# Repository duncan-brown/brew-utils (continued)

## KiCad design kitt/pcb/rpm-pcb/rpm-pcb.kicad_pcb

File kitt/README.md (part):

# kitt

The software that drives the KITT dashboard. Two pieces:

- [`panp/panp.py`](panp/panp.py) — the daemon that runs on both Raspberry Pis
  and puts brewery data onto the dash gauges.
- [`switchpod/`](switchpod/) — Arduino firmware that reads the dash keypads.
  How a pod reaches the Pi is in [switchpod/README.md](switchpod/README.md).

PANP stands for Power / Auto / Norm / Pursuit, the four buttons on the dash.

This file is about how the software works. For what each gauge on the dash
means — KITT's labels against the brewery values behind them — see
[DASHBOARD.md](DASHBOARD.md).

## One script, two Pis

`panp.py` is installed identically on both machines and decides what it is at
startup from `socket.gethostname()`. Anything else exits with an error.

| | `rpints` | `brewpi` |
| --- | --- | --- |
| Loop class | `RPintsLoopHandler` | `BrewPiLoopHandler` |
| Reads | 6 keezer + 3 lager probes, RaspberryPints MySQL | mash + HLT probes, 3 BrewPi Remix instances |
| Drives | tacho, red dummy3, dummy6 | speedo, message center, red/green dummy3 |
| Owns | PANP buttons and lamps, dash power relays, the Hue bench and room lights | flow meter relays |
| Mode GPIO | output (tells `brewpi` the mode) | input (follows `rpints`) |

Shared between them: `read_probe_f` and the `get_temps` thread,
`BrightnessHandler`, `Bus` and `Wire` (the serial ports and the gate that
paces writes to them), `Service` (systemd
notification and shutdown), and the pin constants at the top of the file.
`main()` calls `setup_rpints` or `setup_brewpi` and then runs the loop.

## Structure

Everything slow runs in a daemon thread and communicates with the main loop
through a `Queue`. The main loop never blocks on I/O.

```
  ┌────────────────────┐
  │ get_switchpod()    │  reads /dev/switchpod, one digit per keypress
  ├────────────────────┤
  │ get_temps()        │  polls one-wire probes once a second
  ├────────────────────┤        ┌───────────┐      ┌──────────────┐
  │ get_brewpi_rmx_... │───────▶│  Queues   │─────▶│ loop_handler │────▶ serial
  └────────────────────┘        └───────────┘      │  .loop()     │      to dash
                                                   └──────────────┘
                                                    every 0.25 s
```

Each `loop()` call drains its queues with `drain(q)`, recomputes what should
be on screen, and writes it out. Queue entries are `(index, value)` tuples.

The Hue lights run the other way round: `PANPHandler` queues an on or off
request for the bench light from the button callback, the loop handler
queues one for the room lights when a right-pod key asks, and the
`HueLight.loop()` thread talks to the Hue bridge, which is in another part of
the building. A slow or absent bridge can therefore never hold up the dash.

The database is polled less often than everything else: `RPintsLoopHandler`
counts passes and only queries RaspberryPints once every `DATABASE_EVERY`
passes, which is eleven.

## The PANP modes

Pressing a PANP button on `rpints` moves power relays and flips the two GPIO
lines that `brewpi` watches, so both Pis change behaviour together.

| Mode | Dash | Message center |
| --- | --- | --- |
| **Auto** | off (relays cut power to upper and lower dash) | stays on, showing `BREWPI UP` and flow meter status |
| **Norm** | on, dimmed | captions the lower display |
| **Pursuit** | on, full brightness, switch pod lamps lit, bench light on | captions the lower display |

Leaving Auto clears every display and re-sends brightness, because the boards
were unpowered and have lost their state.

Pursuit also switches on the Hue light strip over the brewery workbench, at
full brightness and a chosen white, so there is enough light to read small
print; Norm and Auto switch it off, as does halting the Pis. Two keys on the
right switch pod, `P IND` and `EJECT R`, switch the brewery's room lights on
and off the same way. `rpints` talks to the Hue bridge's v2 API directly, from
a worker thread. It is optional and is configured by
`/usr/local/etc/panp-hue.json`, which is not in this repository because it
holds the bridge's application key; without the file nothing happens, which
is the case on `brewpi`. Setting it up, including getting a key from the
bridge, choosing the colour temperature and listing the room lights, is in
[panp/README.md](panp/README.md).

The Power button is not software at all. It triggers a latching relay that
switches the whole 12 V supply, and each Pi holds an interlock relay *open*
while it is up, taking the button out of the circuit — so nothing can be
switched off without halting both Pis first. That is `power-relay-*.service`
(opens the interlock at boot) and `power-off-*.sh` (releases it during
shutdown). The wiring is in [../HARDWARE.md](../HARDWARE.md#the-power-button).

## Switch pod buttons

Each switch pod is a resistive keypad read by an Arduino, which prints a
position 0–9 over serial; `panp.py` reads them from `/dev/switchpod` in
`get_switchpod()` and queues them for the loop handler.

Even positions are the pod's left column, odd positions the right — which is
why each handler treats `sp_val` 0/2/4/6/8 as one family and 1/3/5/7/9 as
another. The **right** pod (`rpints`) drives the tacho digits and arc: its
left column is one key per keg, showing the imperial pints left and then the
US gallons left before returning to the keezer mean, its right
column shows the three lager probes, and its last two keys switch the brewery
room lights over the Hue bridge — except that in Pursuit `P IND` cycles the
bench light's colour instead. Coming up from Auto resets the tacho to the
mean. The **left** pod (`brewpi`) selects what the lower speedo display shows
and toggles the flow meter relays. Toggling a flow meter flashes `FLOW n on` on
the message center for a second, then restores the normal caption.

Full button-by-button tables, with photographs of both pods, are in
[DASHBOARD.md](DASHBOARD.md).

## Talking to the dash

The boards are serial slaves at 57600 baud on `/dev/ttyAMA0` and `/dev/ttyAMA1`,
addressed by a letter — `A` tacho, `B` speedo, `C` message center, `E`/`F`
dummy3, `G` dummy6. A command looks like:

```
>ABp3C?
 │││ └── payload: hex byte pairs
 ││└──── register: which value on that board
 │└───── command: B write byte, H write hex sequence, S write string
 └────── destination board
```

so `>ABp3C?` means "tacho, write byte, register p (the seven-segment value),
0x3C". Values are scaled to bytes before sending — `tacho_bar`, `lager_bar`,
`keg_bar` and `temperature_bar` map a temperature or a percentage onto the
bargraph steps by walking a list of thresholds, which is where the dash gets
tuned.

The protocol is Paolo Sancono's and the full specification comes with the
boards — but note that the tacho and speedo registers this code writes are
**not in that specification**. The shipped firmware could not set those displays
from a host at all, so in 2023 the commands were added to it: user-value
registers for the tacho's bars and seven-segment, and for the speedo's two
bargraphs and both digit groups. Paolo holds that modified firmware and is free
to ship it. When one of these commands needs checking, the board firmware is the
authority, not the protocol PDF.

That firmware is confidential to Paolo and is not in this repo. Keep it that
way: describing what a command *does* is fine, quoting or paraphrasing his
source is not.

Two things worth knowing before editing the serial code:

- **Every write is preceded by a 0.1 s gap, and a Pi sends one packet at a
  time across both of its buses.** Without the gap the boards drop messages;
  and the two buses share a level shifter that corrupts a packet on one when
  the other is transmitting. Both rules live in `Bus.write`, which takes a
  first-come-first-served turn on the shared `Wire`, so every write gets the
  gap and a burst from one thread cannot starve the other.
- **Hex payloads must be exactly the right length** — four byte pairs for the
  speedo's upper digits, five for the lower, one per bar for the bargraphs.
  A payload of the wrong length is ignored silently rather than rejected.

## The BrewPi side

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
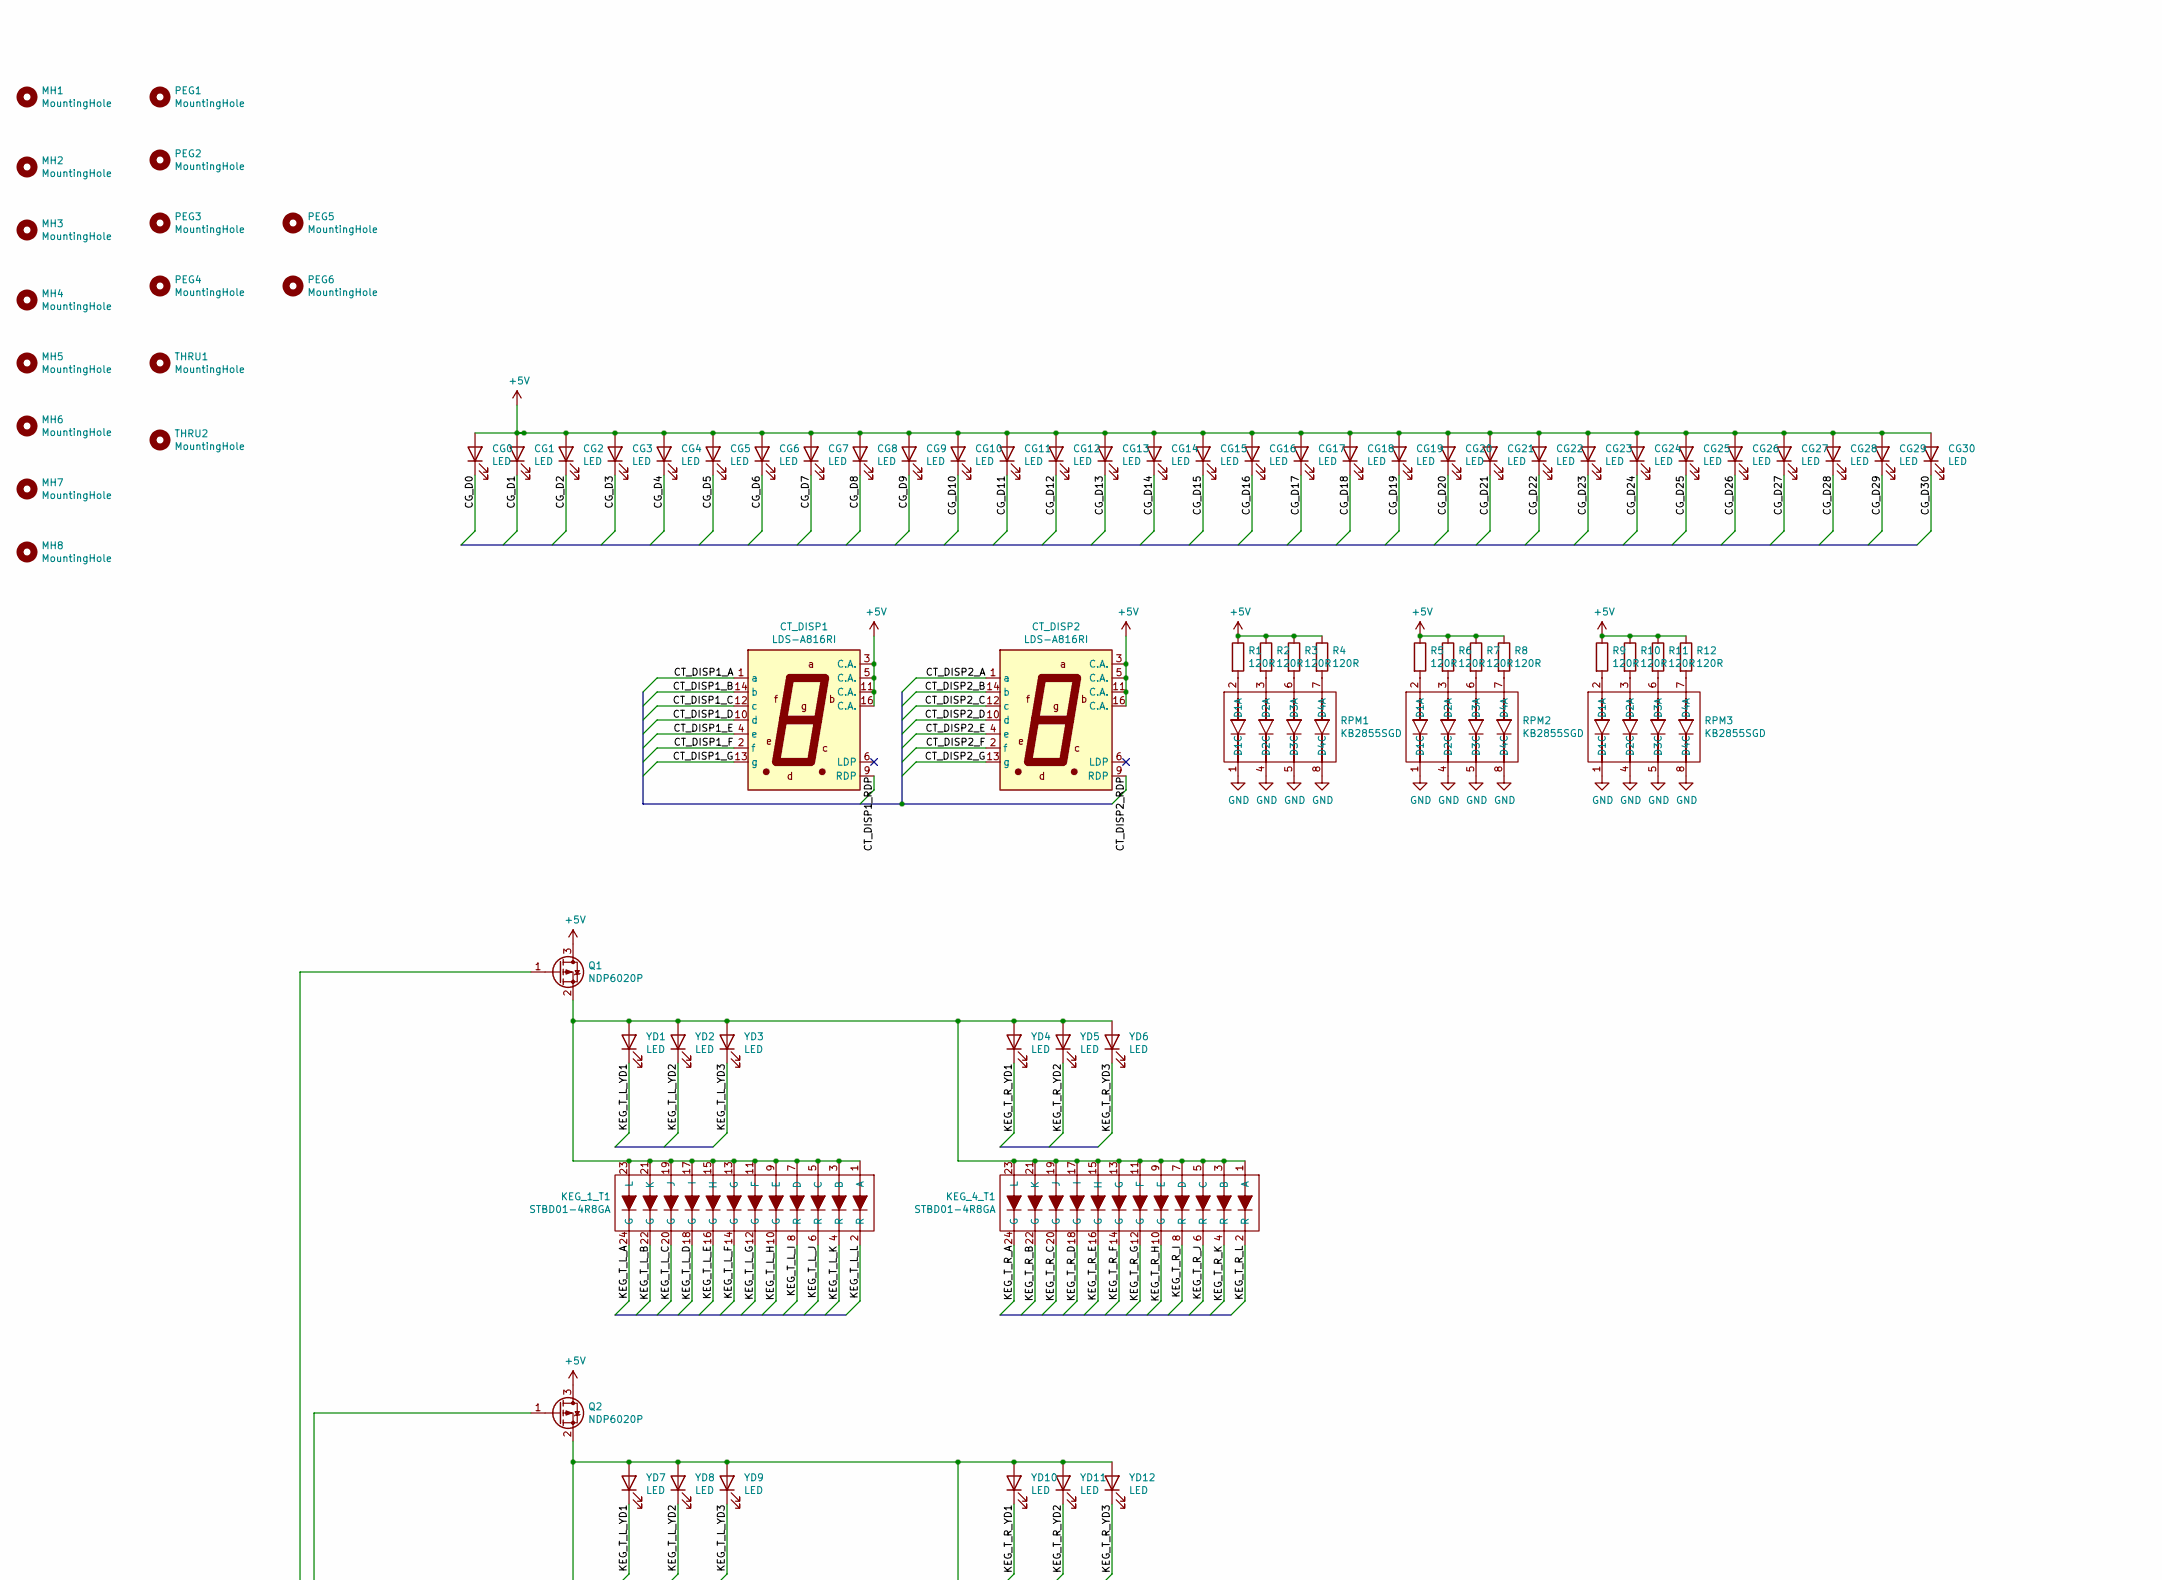
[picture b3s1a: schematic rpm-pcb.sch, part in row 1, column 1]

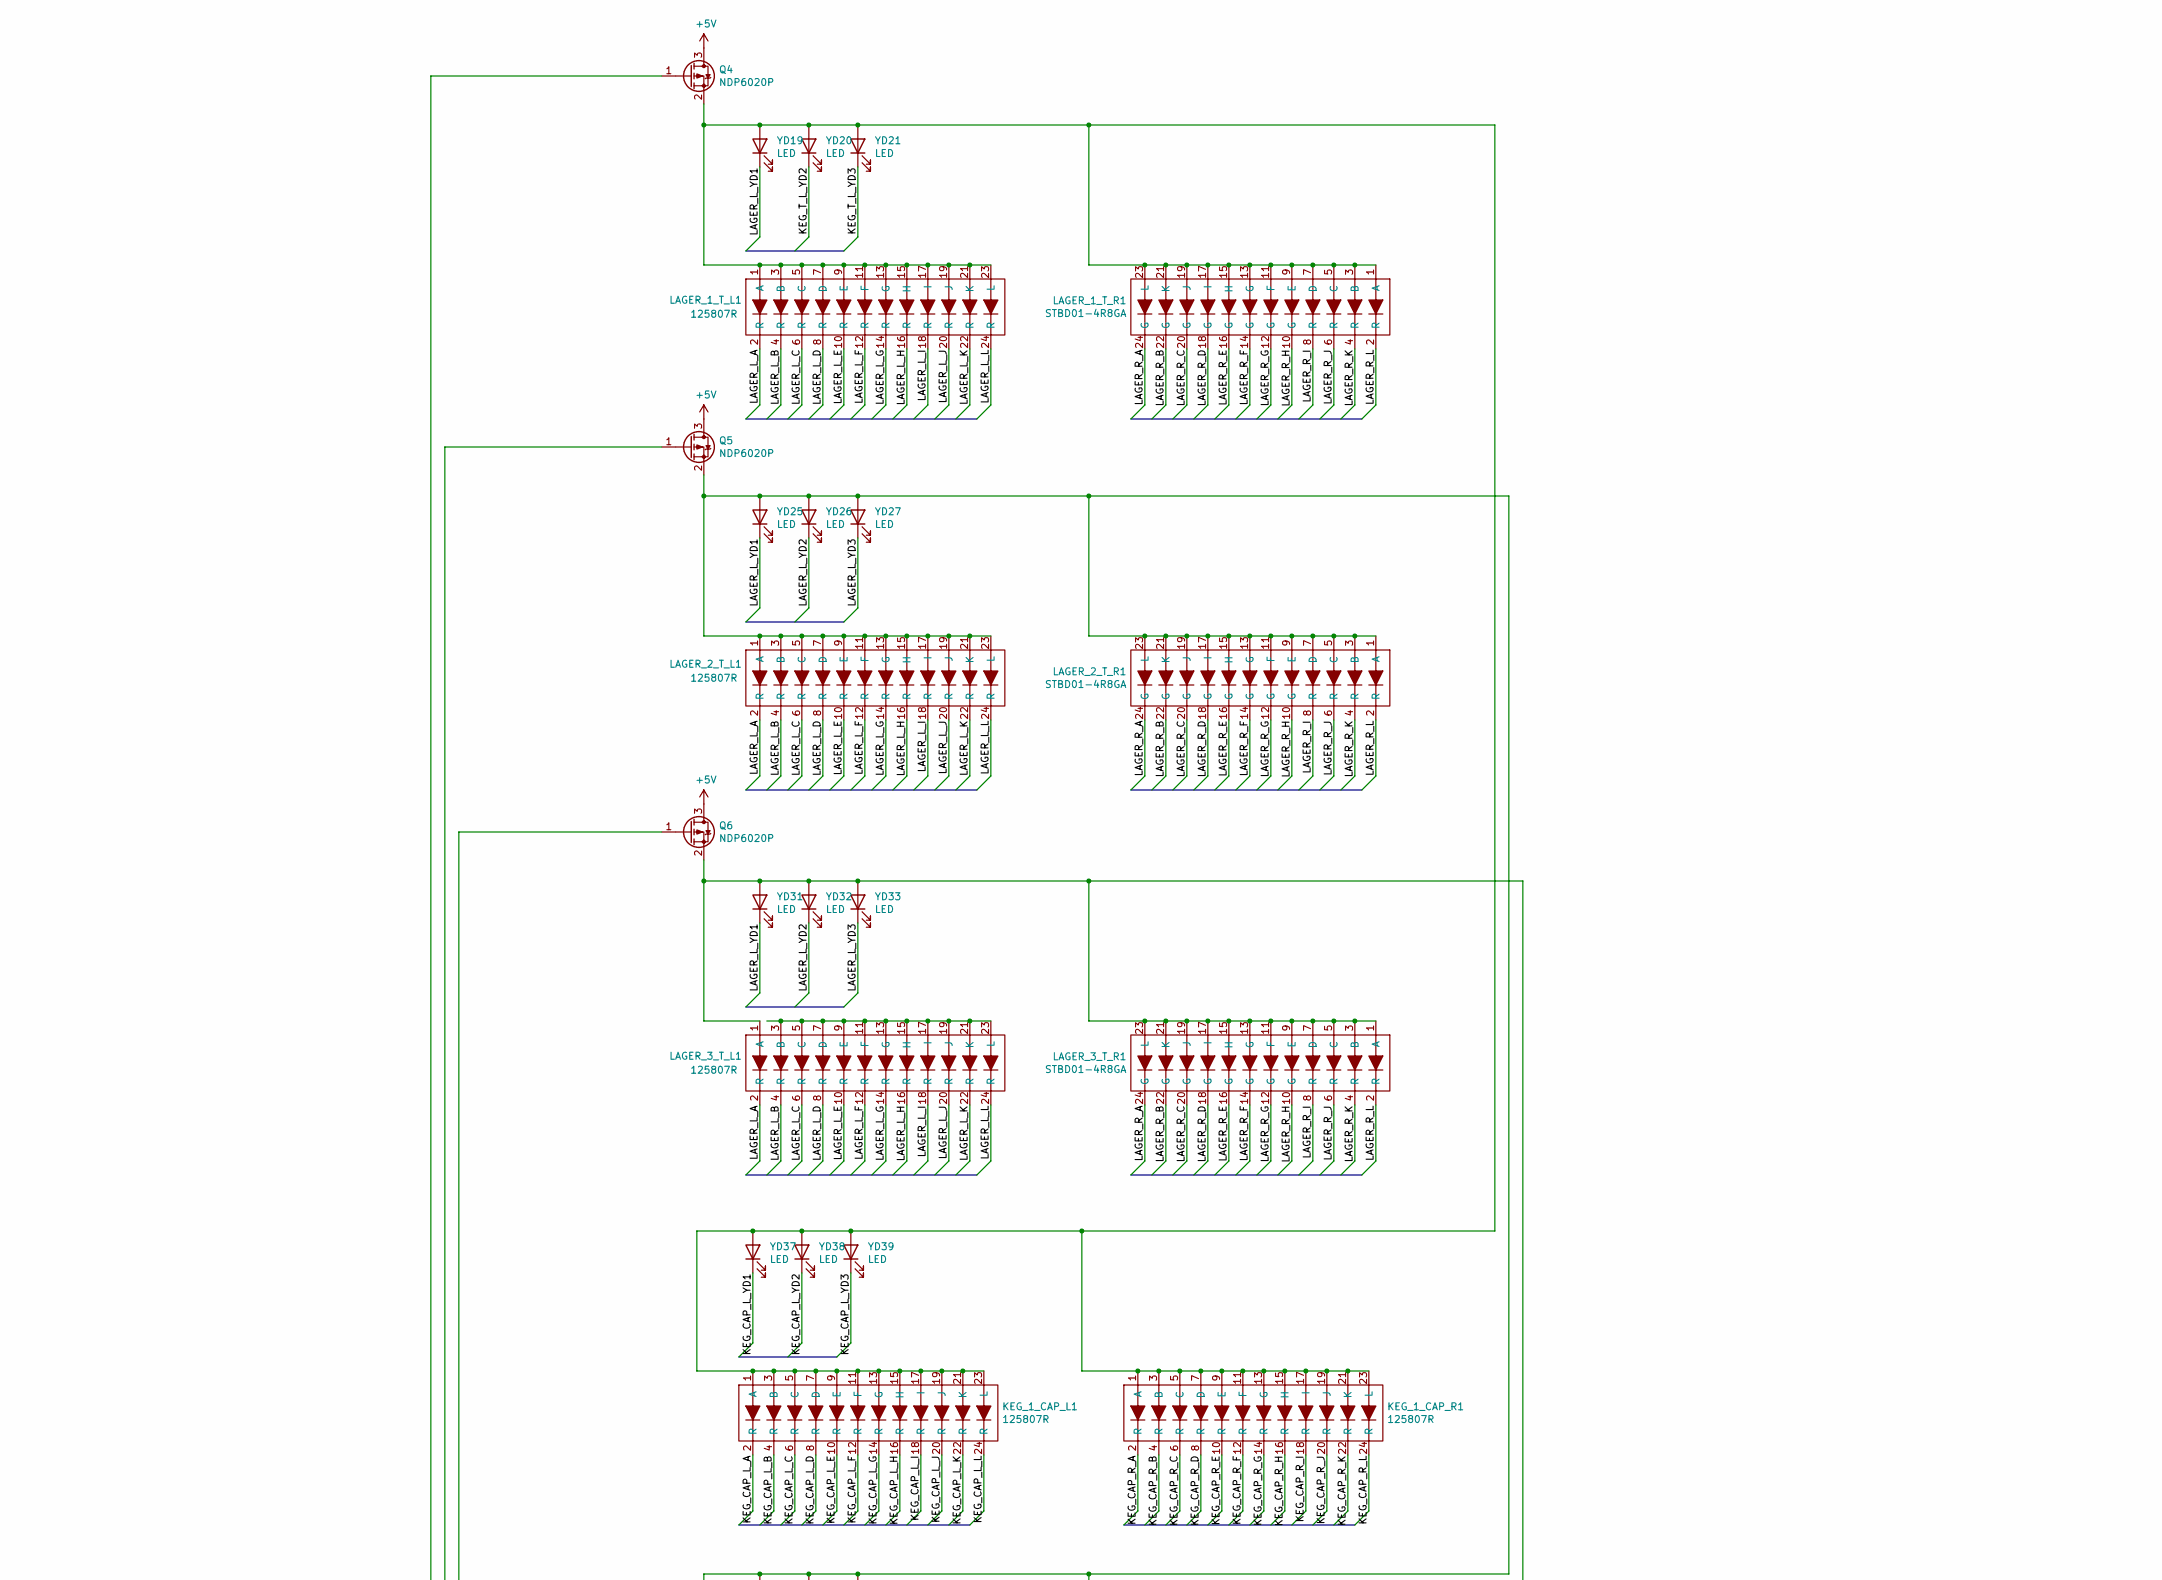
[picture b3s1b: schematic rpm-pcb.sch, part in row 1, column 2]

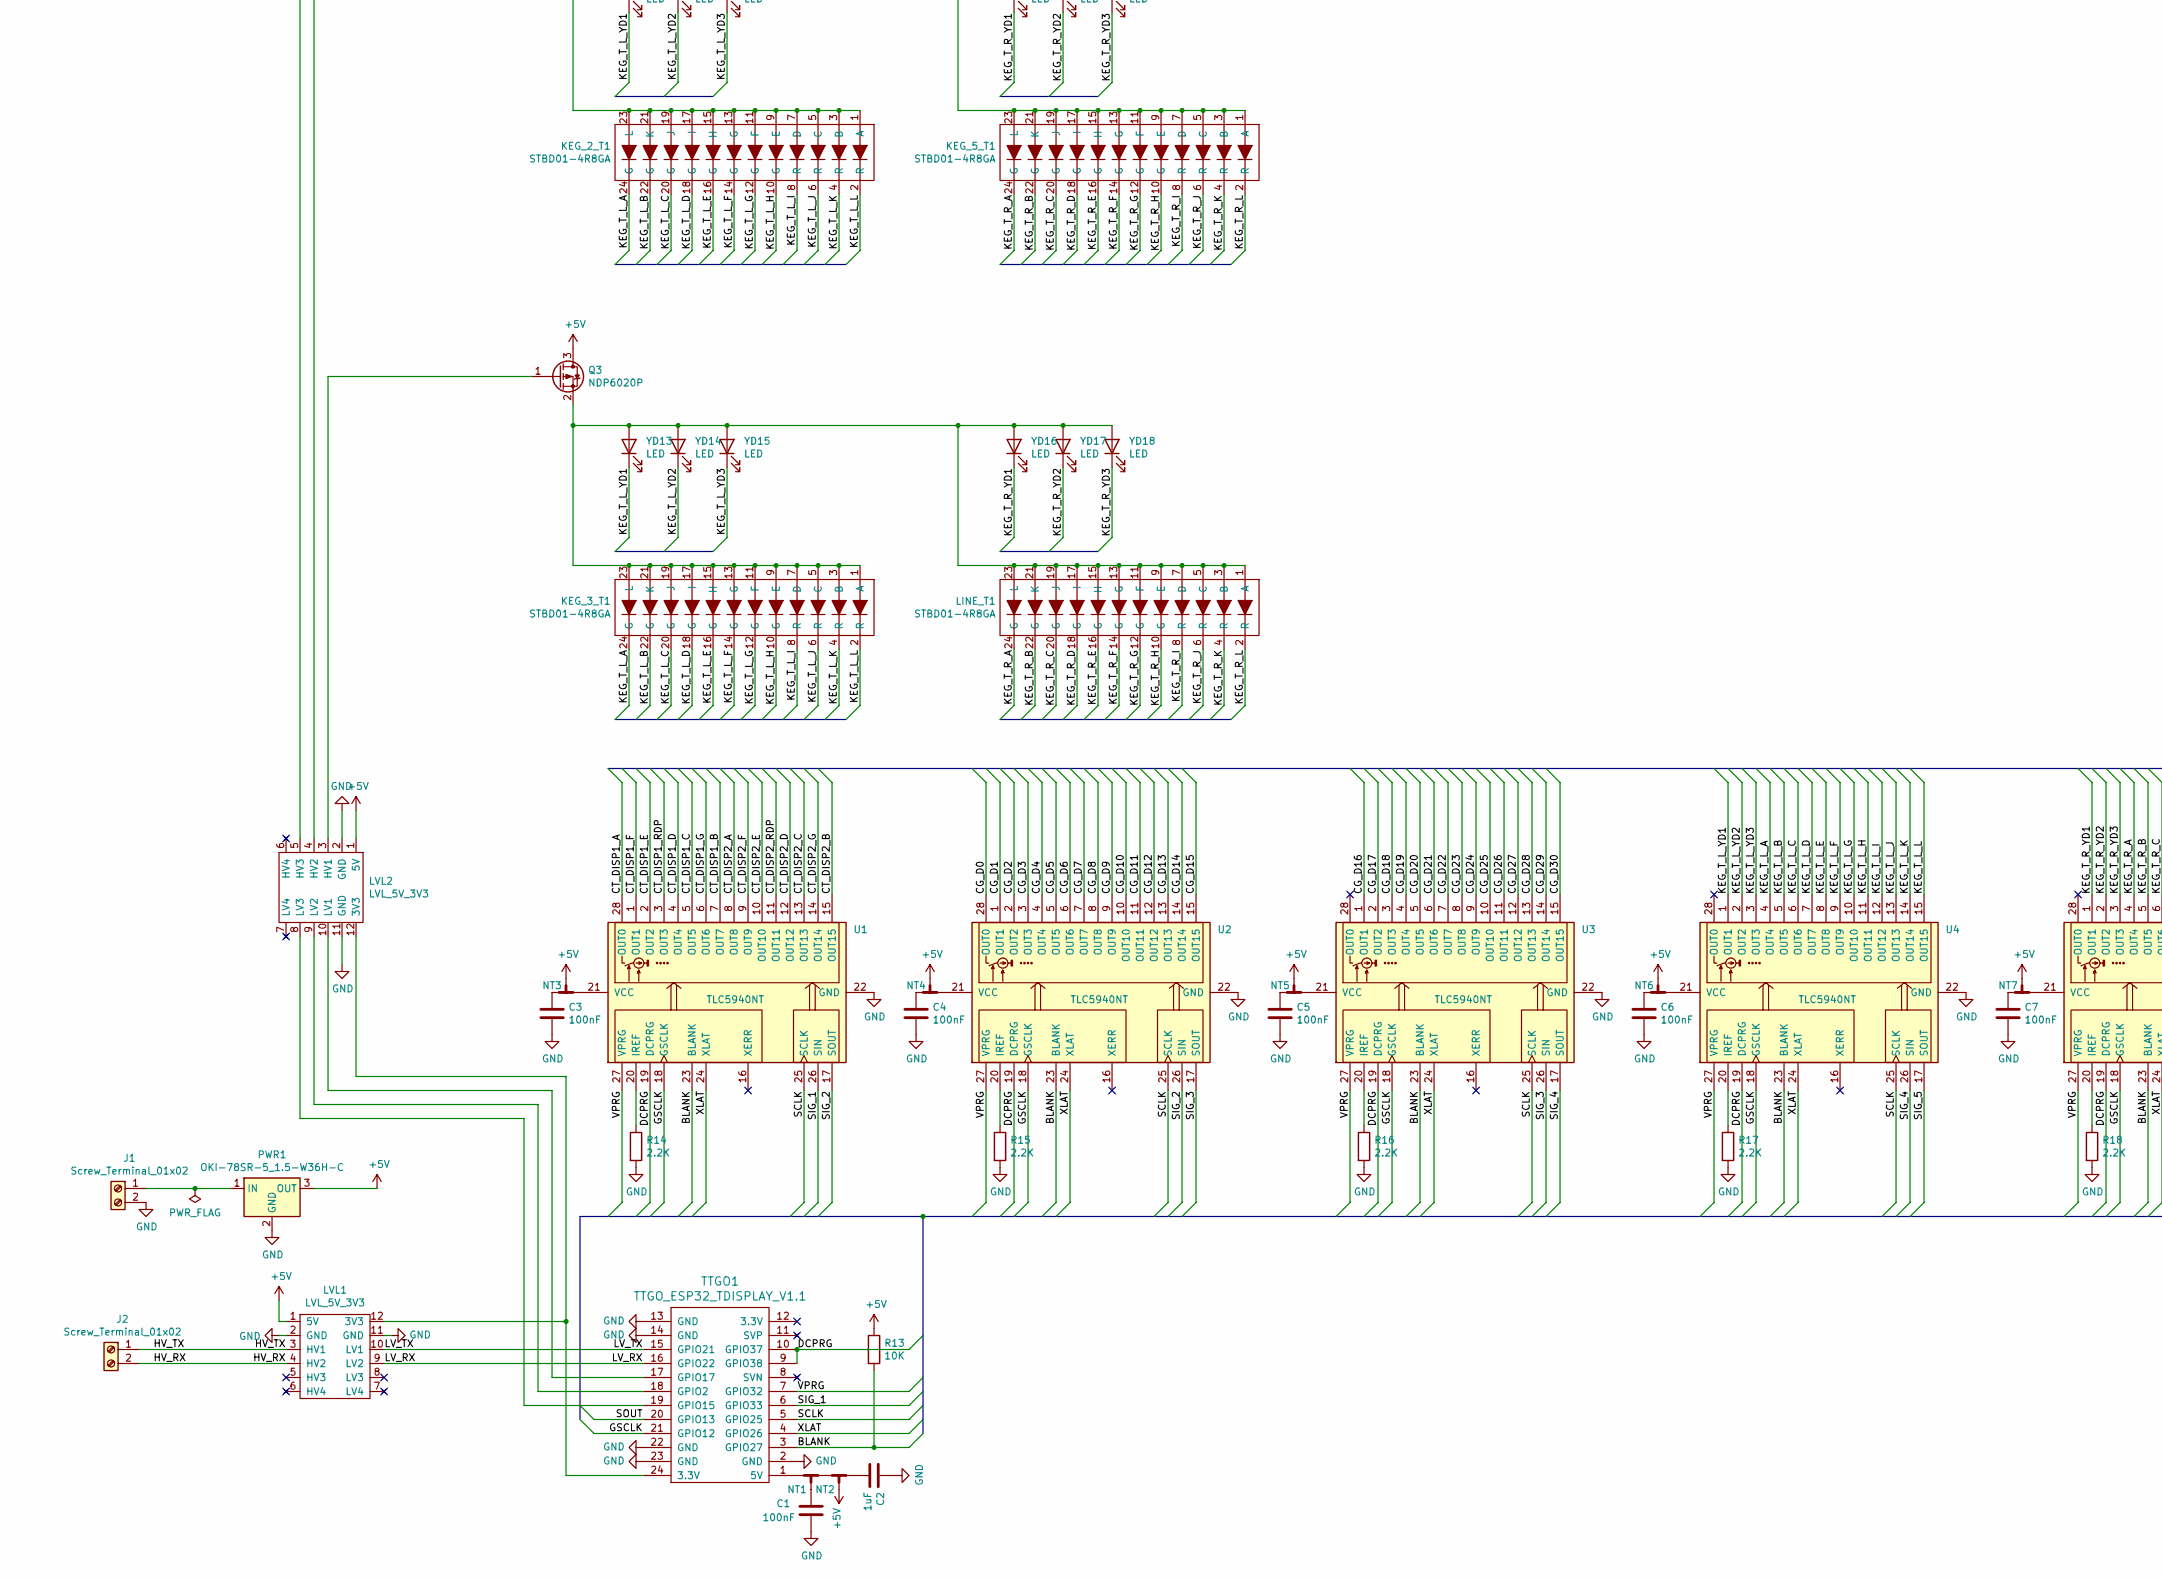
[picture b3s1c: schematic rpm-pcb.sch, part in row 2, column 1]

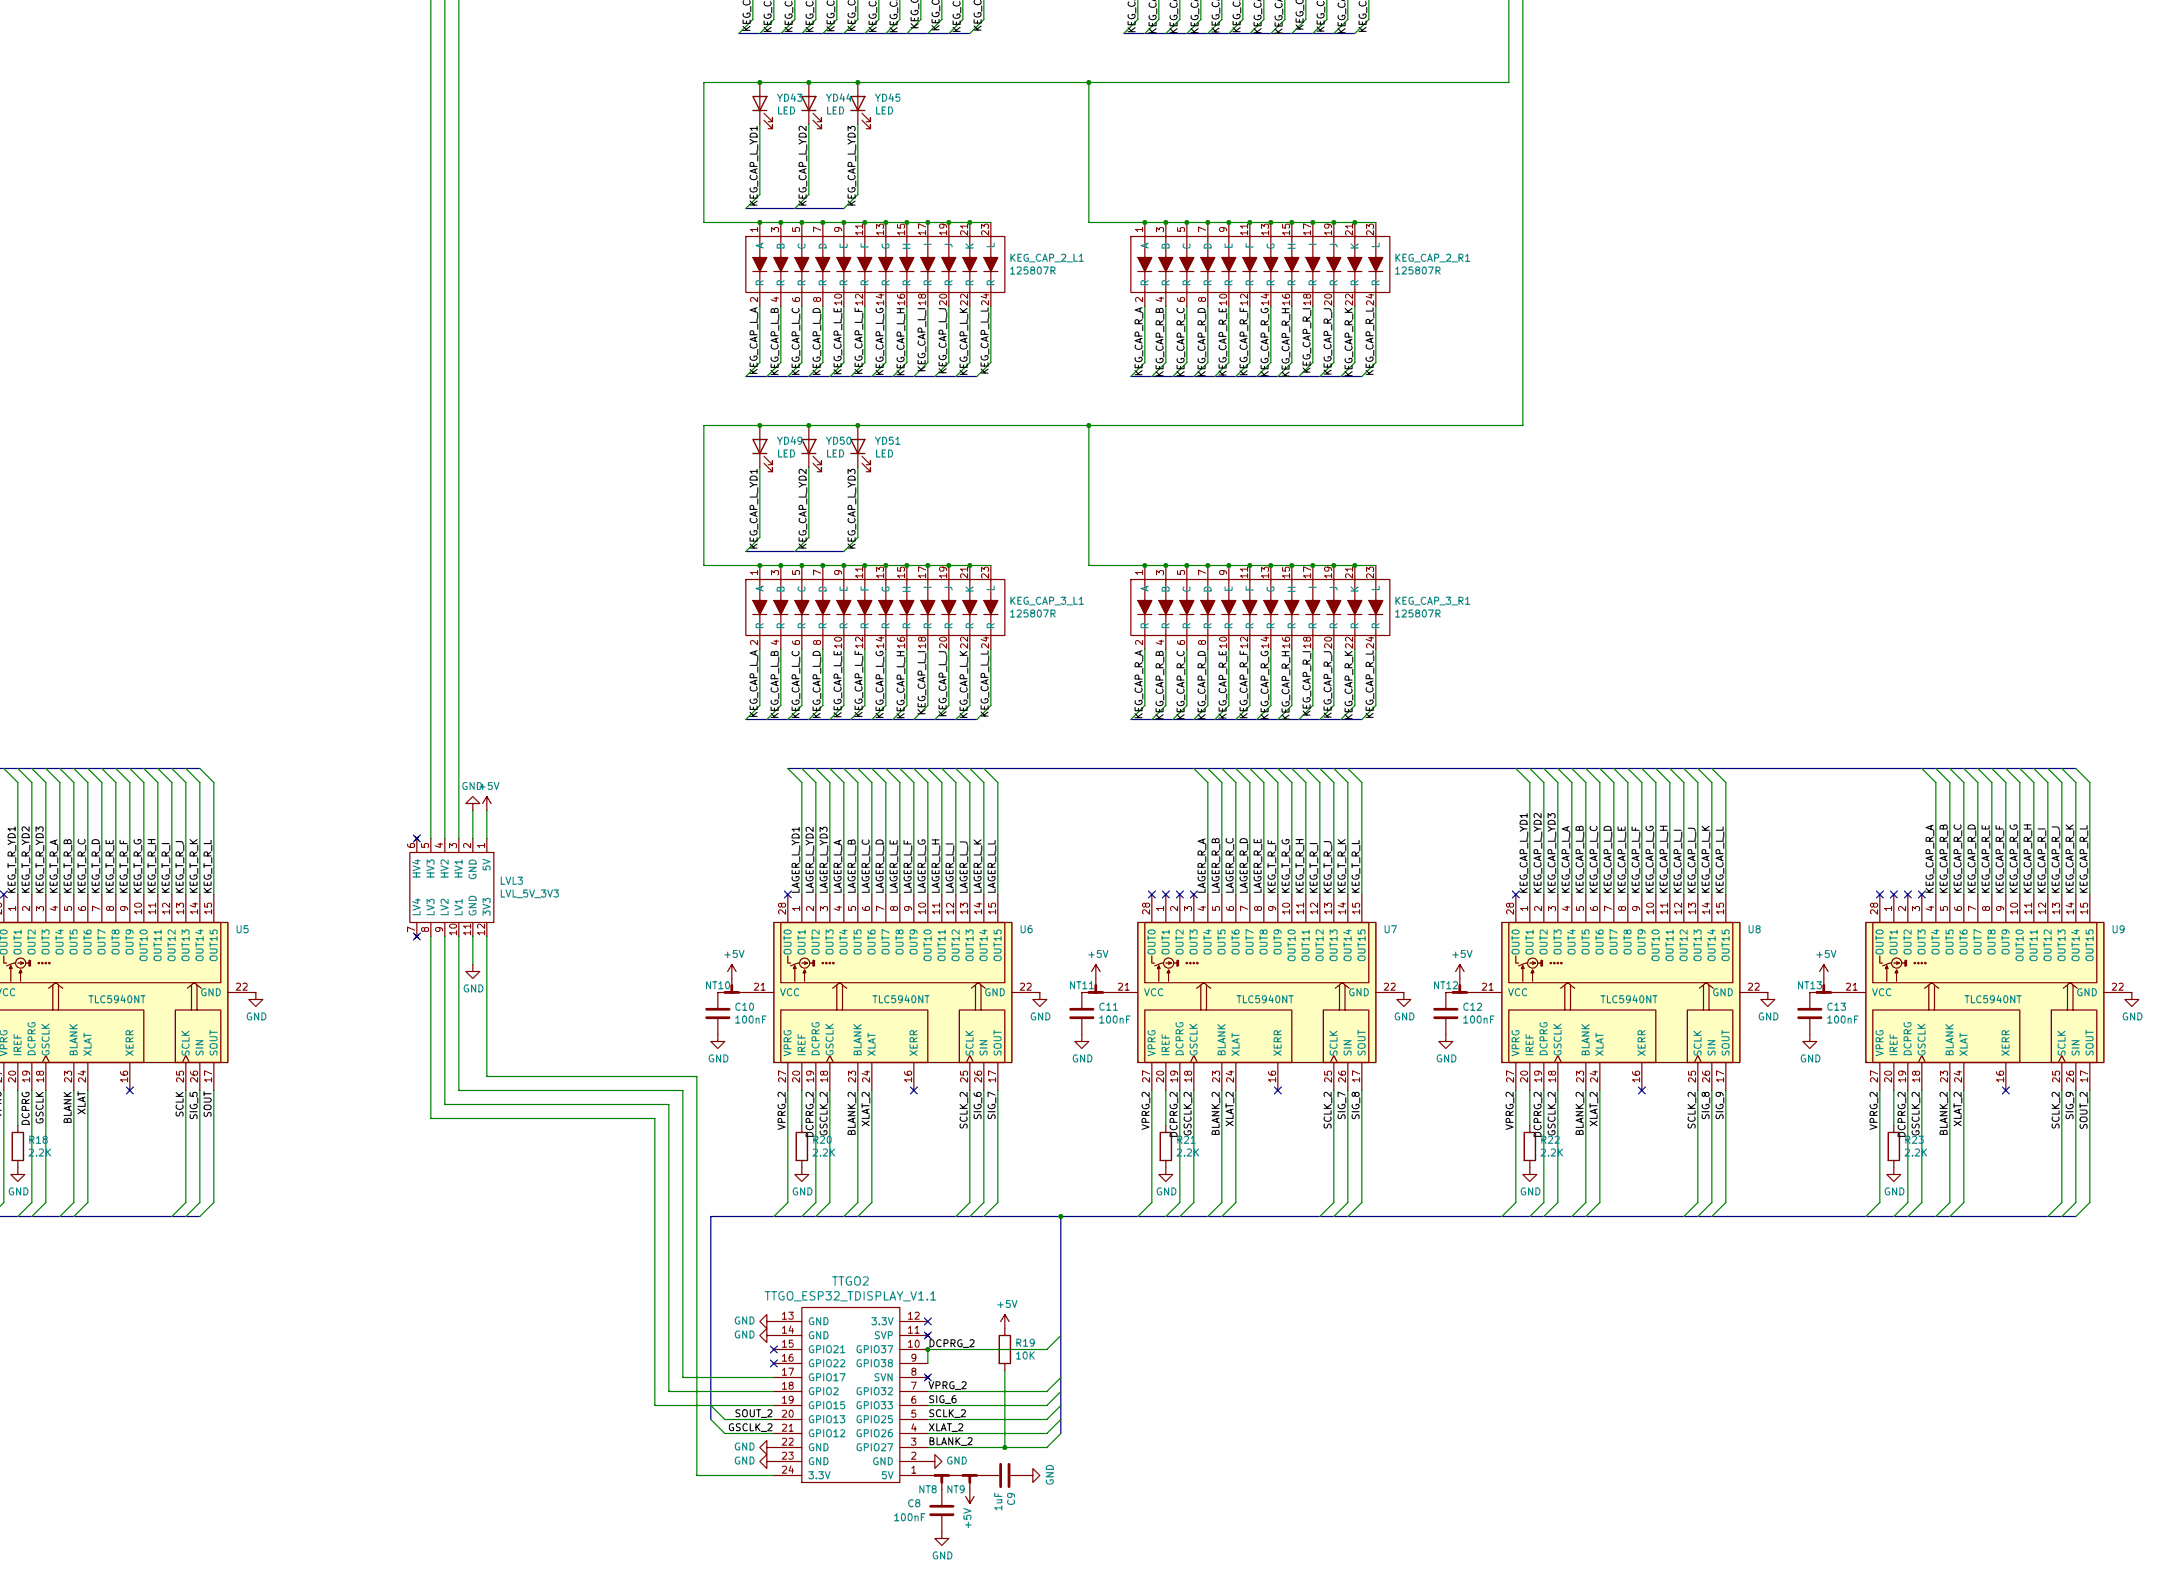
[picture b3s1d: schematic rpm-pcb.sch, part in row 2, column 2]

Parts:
C1, C3, C4, C5, C6, C7, C8, C10, C11, C12, C13: 100nF; C_Rect_L7.0mm_W3.5mm_P5.00mm
C2, C9: 1uF; C_Rect_L7.0mm_W3.5mm_P5.00mm
CG0, CG1, CG2, CG3, CG4, CG5, CG6, CG7, CG8, CG9, CG10, CG11, CG12, CG13, CG14, CG15, CG16, CG17, CG18, CG19, CG20, CG21, CG22, CG23, CG24, CG25, CG26, CG27, CG28, CG29, CG30: LED; Flangeless_LED
CT_DISP1, CT_DISP2: LDS-A816RI
J1, J2: Screw_Terminal_01x02; 5mm_Screw_Terminal_01x02
KEG_1_CAP_L1, KEG_1_CAP_R1: 125807R; LED_12_Segment_2.0mm_24_pin
KEG_1_T1, KEG_2_T1, KEG_3_T1, KEG_4_T1, KEG_5_T1: STBD01-4R8GA; LED_12_Segment_2.0mm_24_pin
KEG_CAP_2_L1, KEG_CAP_2_R1, KEG_CAP_3_L1, KEG_CAP_3_R1: 125807R; LED_12_Segment_2.0mm_24_pin
LAGER_1_T_L1, LAGER_2_T_L1, LAGER_3_T_L1: 125807R; LED_12_Segment_2.0mm_24_pin
LAGER_1_T_R1, LAGER_2_T_R1, LAGER_3_T_R1: STBD01-4R8GA; LED_12_Segment_2.0mm_24_pin
LINE_T1: STBD01-4R8GA; LED_12_Segment_2.0mm_24_pin
LVL1, LVL2, LVL3: LVL_5V_3V3
MH1, MH2, MH3, MH4, MH5, MH6, MH7, MH8: MountingHole; MountingHole_3.2mm_M3
NT1, NT2, NT3, NT4, NT5, NT6, NT7, NT8, NT9, NT10, NT11, NT12, NT13: Net-Tie_3_Tee; NetTie-3_THT_Pad0.3mm
PEG1, PEG2, PEG3, PEG4, PEG5, PEG6: MountingHole; MountingHole_5.3mm_M5
PWR1: OKI-78SR-5_1.5-W36H-C; Converter_DCDC_muRata_OKI-78SR_Horizontal
Q1, Q2, Q3, Q4, Q5, Q6: NDP6020P; TO-220-3_Vertical
R1, R2, R3, R4, R5, R6, R7, R8, R9, R10, R11, R12: 120R; R_Axial_DIN0207_L6.3mm_D2.5mm_P10.16mm_Horizontal
R13, R19: 10K; R_Axial_DIN0207_L6.3mm_D2.5mm_P10.16mm_Horizontal
R14, R15, R16, R17, R18, R20, R21, R22, R23: 2.2K; R_Axial_DIN0207_L6.3mm_D2.5mm_P10.16mm_Horizontal
RPM1, RPM2, RPM3: KB2855SGD; KB2855SGD_Light_Square
THRU1, THRU2: MountingHole; MountingHole_6.4mm_M6
TTGO1, TTGO2: TTGO_ESP32_TDISPLAY_V1.1; TTGO_ESP32_TDisplay_v1.1
U1, U2, U3, U4, U5, U6, U7, U8, U9: TLC5940NT; DIP-28_W7.62mm
YD1, YD2, YD3, YD4, YD5, YD6, YD7, YD8, YD9, YD10, YD11, YD12, YD13, YD14, YD15, YD16, YD17, YD18, YD19, YD20, YD21, YD25, YD26, YD27, YD31, YD32, YD33, YD37, YD38, YD39, YD43, YD44, YD45, YD49, YD50, YD51: LED; Flangeless_LED

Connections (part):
+5V: CG0.2 (A), CG1.2 (A), CG2.2 (A), CG3.2 (A), CG4.2 (A), CG5.2 (A), CG6.2 (A), CG7.2 (A), CG8.2 (A), CG9.2 (A), CG10.2 (A), CG11.2 (A), CG12.2 (A), CG13.2 (A), CG14.2 (A), CG15.2 (A), CG16.2 (A), CG17.2 (A), CG18.2 (A), CG19.2 (A), CG20.2 (A), CG21.2 (A), CG22.2 (A), CG23.2 (A), CG24.2 (A), CG25.2 (A), CG26.2 (A), CG27.2 (A), CG28.2 (A), CG29.2 (A), CG30.2 (A), CT_DISP1.3 (C.A.), CT_DISP1.5 (C.A.), CT_DISP1.11 (C.A.), CT_DISP1.16 (C.A.), CT_DISP2.3 (C.A.), CT_DISP2.5 (C.A.), CT_DISP2.11 (C.A.), CT_DISP2.16 (C.A.), LVL1.1 (5V), LVL2.1 (5V), LVL3.1 (5V), NT2.3, NT3.3, NT4.3, NT5.3, NT6.3, NT7.3, NT9.3, NT10.3, NT11.3, NT12.3, NT13.3, PWR1.3 (OUT), Q1.3 (D), Q2.3 (D), Q3.3 (D), Q4.3 (D), Q5.3 (D), Q6.3 (D), R1.1, R2.1, R3.1, R4.1, R5.1, R6.1, R7.1, R8.1, R9.1, R10.1, R11.1, R12.1, R13.1, R19.1
/BLANK: R13.2, TTGO1.3 (GPIO27), U1.23 (BLANK), U2.23 (BLANK), U3.23 (BLANK), U4.23 (BLANK), U5.23 (BLANK)
/BLANK_2: R19.2, TTGO2.3 (GPIO27), U6.23 (BLANK), U7.23 (BLANK), U8.23 (BLANK), U9.23 (BLANK)
/CG_D0: CG0.1 (K), U2.28 (OUT0)
/CG_D1: CG1.1 (K), U2.1 (OUT1)
/CG_D2: CG2.1 (K), U2.2 (OUT2)
/CG_D3: CG3.1 (K), U2.3 (OUT3)
/CG_D4: CG4.1 (K), U2.4 (OUT4)
/CG_D5: CG5.1 (K), U2.5 (OUT5)
/CG_D6: CG6.1 (K), U2.6 (OUT6)
/CG_D7: CG7.1 (K), U2.7 (OUT7)
/CG_D8: CG8.1 (K), U2.8 (OUT8)
/CG_D9: CG9.1 (K), U2.9 (OUT9)
/CG_D10: CG10.1 (K), U2.10 (OUT10)
/CG_D11: CG11.1 (K), U2.11 (OUT11)
/CG_D12: CG12.1 (K), U2.12 (OUT12)
/CG_D13: CG13.1 (K), U2.13 (OUT13)
/CG_D14: CG14.1 (K), U2.14 (OUT14)
/CG_D15: CG15.1 (K), U2.15 (OUT15)
/CG_D16: CG16.1 (K), U3.1 (OUT1)
/CG_D17: CG17.1 (K), U3.2 (OUT2)
/CG_D18: CG18.1 (K), U3.3 (OUT3)
/CG_D19: CG19.1 (K), U3.4 (OUT4)
/CG_D20: CG20.1 (K), U3.5 (OUT5)
/CG_D21: CG21.1 (K), U3.6 (OUT6)
/CG_D22: CG22.1 (K), U3.7 (OUT7)
/CG_D23: CG23.1 (K), U3.8 (OUT8)
/CG_D24: CG24.1 (K), U3.9 (OUT9)
/CG_D25: CG25.1 (K), U3.10 (OUT10)
/CG_D26: CG26.1 (K), U3.11 (OUT11)
/CG_D27: CG27.1 (K), U3.12 (OUT12)
/CG_D28: CG28.1 (K), U3.13 (OUT13)
/CG_D29: CG29.1 (K), U3.14 (OUT14)
/CG_D30: CG30.1 (K), U3.15 (OUT15)
/CT_DISP1_A: CT_DISP1.1 (a), U1.28 (OUT0)
/CT_DISP1_B: CT_DISP1.14 (b), U1.7 (OUT7)
/CT_DISP1_C: CT_DISP1.12 (c), U1.5 (OUT5)
/CT_DISP1_D: CT_DISP1.10 (d), U1.4 (OUT4)
/CT_DISP1_E: CT_DISP1.4 (e), U1.2 (OUT2)
/CT_DISP1_F: CT_DISP1.2 (f), U1.1 (OUT1)
/CT_DISP1_G: CT_DISP1.13 (g), U1.6 (OUT6)
/CT_DISP1_RDP: CT_DISP1.9 (RDP), U1.3 (OUT3)
/CT_DISP2_A: CT_DISP2.1 (a), U1.8 (OUT8)
/CT_DISP2_B: CT_DISP2.14 (b), U1.15 (OUT15)
/CT_DISP2_C: CT_DISP2.12 (c), U1.13 (OUT13)
/CT_DISP2_D: CT_DISP2.10 (d), U1.12 (OUT12)
/CT_DISP2_E: CT_DISP2.4 (e), U1.10 (OUT10)
/CT_DISP2_F: CT_DISP2.2 (f), U1.9 (OUT9)
/CT_DISP2_G: CT_DISP2.13 (g), U1.14 (OUT14)
/CT_DISP2_RDP: CT_DISP2.9 (RDP), U1.11 (OUT11)
/DCPRG: TTGO1.9 (GPIO38), TTGO1.10 (GPIO37), U1.19 (DCPRG), U2.19 (DCPRG), U3.19 (DCPRG), U4.19 (DCPRG), U5.19 (DCPRG)
/DCPRG_2: TTGO2.9 (GPIO38), TTGO2.10 (GPIO37), U6.19 (DCPRG), U7.19 (DCPRG), U8.19 (DCPRG), U9.19 (DCPRG)
/GSCLK: TTGO1.21 (GPIO12), U1.18 (GSCLK), U2.18 (GSCLK), U3.18 (GSCLK), U4.18 (GSCLK), U5.18 (GSCLK)
/GSCLK_2: TTGO2.21 (GPIO12), U6.18 (GSCLK), U7.18 (GSCLK), U8.18 (GSCLK), U9.18 (GSCLK)
/HV_RX: J2.2, LVL1.4 (HV2)
/HV_TX: J2.1, LVL1.3 (HV1)
/KEG_CAP_L_A: KEG_1_CAP_L1.2 (R), KEG_CAP_2_L1.2 (R), KEG_CAP_3_L1.2 (R), U8.4 (OUT4)
/KEG_CAP_L_B: KEG_1_CAP_L1.4 (R), KEG_CAP_2_L1.4 (R), KEG_CAP_3_L1.4 (R), U8.5 (OUT5)
/KEG_CAP_L_C: KEG_1_CAP_L1.6 (R), KEG_CAP_2_L1.6 (R), KEG_CAP_3_L1.6 (R), U8.6 (OUT6)
/KEG_CAP_L_D: KEG_1_CAP_L1.8 (R), KEG_CAP_2_L1.8 (R), KEG_CAP_3_L1.8 (R), U8.7 (OUT7)
/KEG_CAP_L_E: KEG_1_CAP_L1.10 (R), KEG_CAP_2_L1.10 (R), KEG_CAP_3_L1.10 (R), U8.8 (OUT8)
/KEG_CAP_L_F: KEG_1_CAP_L1.12 (R), KEG_CAP_2_L1.12 (R), KEG_CAP_3_L1.12 (R), U8.9 (OUT9)
/KEG_CAP_L_G: KEG_1_CAP_L1.14 (R), KEG_CAP_2_L1.14 (R), KEG_CAP_3_L1.14 (R), U8.10 (OUT10)
/KEG_CAP_L_H: KEG_1_CAP_L1.16 (R), KEG_CAP_2_L1.16 (R), KEG_CAP_3_L1.16 (R), U8.11 (OUT11)
/KEG_CAP_L_I: KEG_1_CAP_L1.18 (R), KEG_CAP_2_L1.18 (R), KEG_CAP_3_L1.18 (R), U8.12 (OUT12)
/KEG_CAP_L_J: KEG_1_CAP_L1.20 (R), KEG_CAP_2_L1.20 (R), KEG_CAP_3_L1.20 (R), U8.13 (OUT13)
/KEG_CAP_L_K: KEG_1_CAP_L1.22 (R), KEG_CAP_2_L1.22 (R), KEG_CAP_3_L1.22 (R), U8.14 (OUT14)
/KEG_CAP_L_L: KEG_1_CAP_L1.24 (R), KEG_CAP_2_L1.24 (R), KEG_CAP_3_L1.24 (R), U8.15 (OUT15)
/KEG_CAP_L_YD1: U8.1 (OUT1), YD37.1 (K), YD43.1 (K), YD49.1 (K)
/KEG_CAP_L_YD2: U8.2 (OUT2), YD38.1 (K), YD44.1 (K), YD50.1 (K)
/KEG_CAP_L_YD3: U8.3 (OUT3), YD39.1 (K), YD45.1 (K), YD51.1 (K)
/KEG_CAP_R_A: KEG_1_CAP_R1.2 (R), KEG_CAP_2_R1.2 (R), KEG_CAP_3_R1.2 (R), U9.4 (OUT4)
/KEG_CAP_R_B: KEG_1_CAP_R1.4 (R), KEG_CAP_2_R1.4 (R), KEG_CAP_3_R1.4 (R), U9.5 (OUT5)
/KEG_CAP_R_C: KEG_1_CAP_R1.6 (R), KEG_CAP_2_R1.6 (R), KEG_CAP_3_R1.6 (R), U9.6 (OUT6)
/KEG_CAP_R_D: KEG_1_CAP_R1.8 (R), KEG_CAP_2_R1.8 (R), KEG_CAP_3_R1.8 (R), U9.7 (OUT7)
/KEG_CAP_R_E: KEG_1_CAP_R1.10 (R), KEG_CAP_2_R1.10 (R), KEG_CAP_3_R1.10 (R), U9.8 (OUT8)
/KEG_CAP_R_F: KEG_1_CAP_R1.12 (R), KEG_CAP_2_R1.12 (R), KEG_CAP_3_R1.12 (R), U9.9 (OUT9)
/KEG_CAP_R_G: KEG_1_CAP_R1.14 (R), KEG_CAP_2_R1.14 (R), KEG_CAP_3_R1.14 (R), U9.10 (OUT10)
/KEG_CAP_R_H: KEG_1_CAP_R1.16 (R), KEG_CAP_2_R1.16 (R), KEG_CAP_3_R1.16 (R), U9.11 (OUT11)
/KEG_CAP_R_I: KEG_1_CAP_R1.18 (R), KEG_CAP_2_R1.18 (R), KEG_CAP_3_R1.18 (R), U9.12 (OUT12)
/KEG_CAP_R_J: KEG_1_CAP_R1.20 (R), KEG_CAP_2_R1.20 (R), KEG_CAP_3_R1.20 (R), U9.13 (OUT13)
/KEG_CAP_R_K: KEG_1_CAP_R1.22 (R), KEG_CAP_2_R1.22 (R), KEG_CAP_3_R1.22 (R), U9.14 (OUT14)
/KEG_CAP_R_L: KEG_1_CAP_R1.24 (R), KEG_CAP_2_R1.24 (R), KEG_CAP_3_R1.24 (R), U9.15 (OUT15)
/KEG_T_L_A: KEG_1_T1.24 (G), KEG_2_T1.24 (G), KEG_3_T1.24 (G), U4.4 (OUT4)
/KEG_T_L_B: KEG_1_T1.22 (G), KEG_2_T1.22 (G), KEG_3_T1.22 (G), U4.5 (OUT5)
/KEG_T_L_C: KEG_1_T1.20 (G), KEG_2_T1.20 (G), KEG_3_T1.20 (G), U4.6 (OUT6)
/KEG_T_L_D: KEG_1_T1.18 (G), KEG_2_T1.18 (G), KEG_3_T1.18 (G), U4.7 (OUT7)
/KEG_T_L_E: KEG_1_T1.16 (G), KEG_2_T1.16 (G), KEG_3_T1.16 (G), U4.8 (OUT8)
/KEG_T_L_F: KEG_1_T1.14 (G), KEG_2_T1.14 (G), KEG_3_T1.14 (G), U4.9 (OUT9)
/KEG_T_L_G: KEG_1_T1.12 (G), KEG_2_T1.12 (G), KEG_3_T1.12 (G), U4.10 (OUT10)
/KEG_T_L_H: KEG_1_T1.10 (G), KEG_2_T1.10 (G), KEG_3_T1.10 (G), U4.11 (OUT11)
/KEG_T_L_I: KEG_1_T1.8 (R), KEG_2_T1.8 (R), KEG_3_T1.8 (R), U4.12 (OUT12)
/KEG_T_L_J: KEG_1_T1.6 (R), KEG_2_T1.6 (R), KEG_3_T1.6 (R), U4.13 (OUT13)
/KEG_T_L_K: KEG_1_T1.4 (R), KEG_2_T1.4 (R), KEG_3_T1.4 (R), U4.14 (OUT14)
/KEG_T_L_L: KEG_1_T1.2 (R), KEG_2_T1.2 (R), KEG_3_T1.2 (R), U4.15 (OUT15)
/KEG_T_L_YD1: U4.1 (OUT1), YD1.1 (K), YD7.1 (K), YD13.1 (K)
/KEG_T_L_YD2: U4.2 (OUT2), YD2.1 (K), YD8.1 (K), YD14.1 (K), YD20.1 (K)
/KEG_T_L_YD3: U4.3 (OUT3), YD3.1 (K), YD9.1 (K), YD15.1 (K), YD21.1 (K)
/KEG_T_R_A: KEG_4_T1.24 (G), KEG_5_T1.24 (G), LINE_T1.24 (G), U5.4 (OUT4)
/KEG_T_R_B: KEG_4_T1.22 (G), KEG_5_T1.22 (G), LINE_T1.22 (G), U5.5 (OUT5)
/KEG_T_R_C: KEG_4_T1.20 (G), KEG_5_T1.20 (G), LINE_T1.20 (G), U5.6 (OUT6)
/KEG_T_R_D: KEG_4_T1.18 (G), KEG_5_T1.18 (G), LINE_T1.18 (G), U5.7 (OUT7)
/KEG_T_R_E: KEG_4_T1.16 (G), KEG_5_T1.16 (G), LINE_T1.16 (G), U5.8 (OUT8)
/KEG_T_R_F: KEG_4_T1.14 (G), KEG_5_T1.14 (G), LINE_T1.14 (G), U5.9 (OUT9), U7.9 (OUT9)
/KEG_T_R_G: KEG_4_T1.12 (G), KEG_5_T1.12 (G), LINE_T1.12 (G), U5.10 (OUT10), U7.10 (OUT10)
/KEG_T_R_H: KEG_4_T1.10 (G), KEG_5_T1.10 (G), LINE_T1.10 (G), U5.11 (OUT11), U7.11 (OUT11)
/KEG_T_R_I: KEG_4_T1.8 (R), KEG_5_T1.8 (R), LINE_T1.8 (R), U5.12 (OUT12), U7.12 (OUT12)
/KEG_T_R_J: KEG_4_T1.6 (R), KEG_5_T1.6 (R), LINE_T1.6 (R), U5.13 (OUT13), U7.13 (OUT13)
/KEG_T_R_K: KEG_4_T1.4 (R), KEG_5_T1.4 (R), LINE_T1.4 (R), U5.14 (OUT14), U7.14 (OUT14)
/KEG_T_R_L: KEG_4_T1.2 (R), KEG_5_T1.2 (R), LINE_T1.2 (R), U5.15 (OUT15), U7.15 (OUT15)
/KEG_T_R_YD1: U5.1 (OUT1), YD4.1 (K), YD10.1 (K), YD16.1 (K)
/KEG_T_R_YD2: U5.2 (OUT2), YD5.1 (K), YD11.1 (K), YD17.1 (K)
/KEG_T_R_YD3: U5.3 (OUT3), YD6.1 (K), YD12.1 (K), YD18.1 (K)
/LAGER_L_A: LAGER_1_T_L1.2 (R), LAGER_2_T_L1.2 (R), LAGER_3_T_L1.2 (R), U6.4 (OUT4)
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
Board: 2 copper layers, 178 parts (0 on the bottom side), 229 nets, no tracks yet.

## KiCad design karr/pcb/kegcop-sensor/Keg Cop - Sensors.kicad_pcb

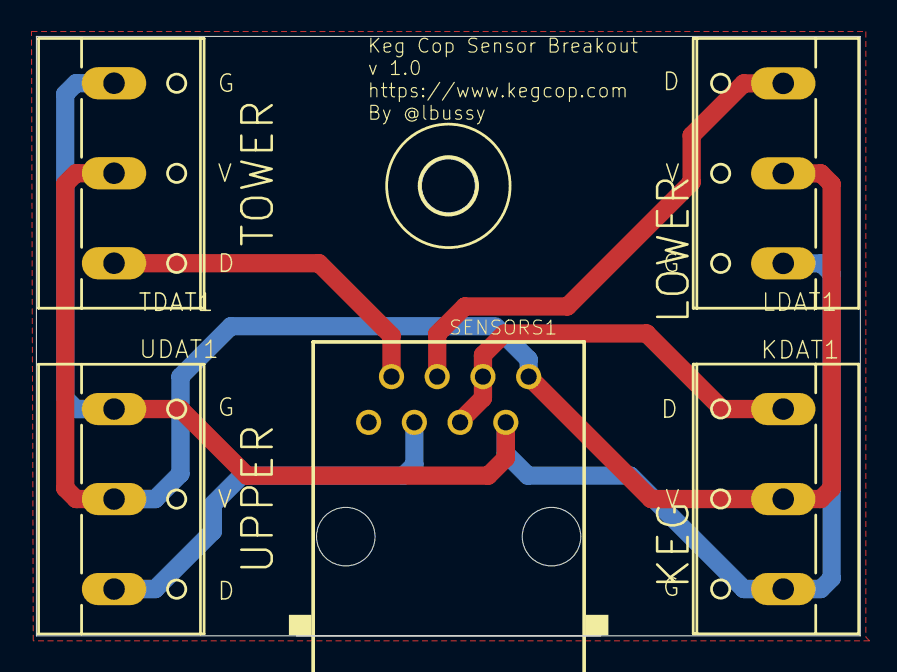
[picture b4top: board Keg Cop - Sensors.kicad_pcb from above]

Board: 2 copper layers, 45.8 x 33.3 mm, 6 parts (0 on the bottom side), 6 nets.

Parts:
KDAT1: W237-103
LDAT1: W237-103
SENSORS1: RJ45; RJ45-NO-SHIELD
TDAT1: W237-103
U$1: 3,0
UDAT1: W237-103

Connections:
/5V: KDAT1.2, LDAT1.2, SENSORS1.8, TDAT1.2, UDAT1.2
/GND: KDAT1.1, LDAT1.1, SENSORS1.7, TDAT1.1, UDAT1.1
/KDAT: KDAT1.3, SENSORS1.5, SENSORS1.6
/LDAT: LDAT1.3, SENSORS1.4
/TDAT: SENSORS1.2, TDAT1.3
/UDAT: SENSORS1.3, UDAT1.3
